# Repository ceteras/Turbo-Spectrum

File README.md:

# Turbo Spectrum aka CoBra 2

You can find out everything about Turbo Spectrum on [cobrasov.org](https://cobrasov.org), including project history, documentation, DipTrace project and gerbers, source code and binaries.  

This repo hosts the Kicad 8 port of the original project.  
This is not really ready for production, it was done for educational purposes.    

© 2022 The Cismas Foundation   
  
Mainboard render from Kicad:

This is my board, assembled from an original kit  made by the Cismas Foundation.

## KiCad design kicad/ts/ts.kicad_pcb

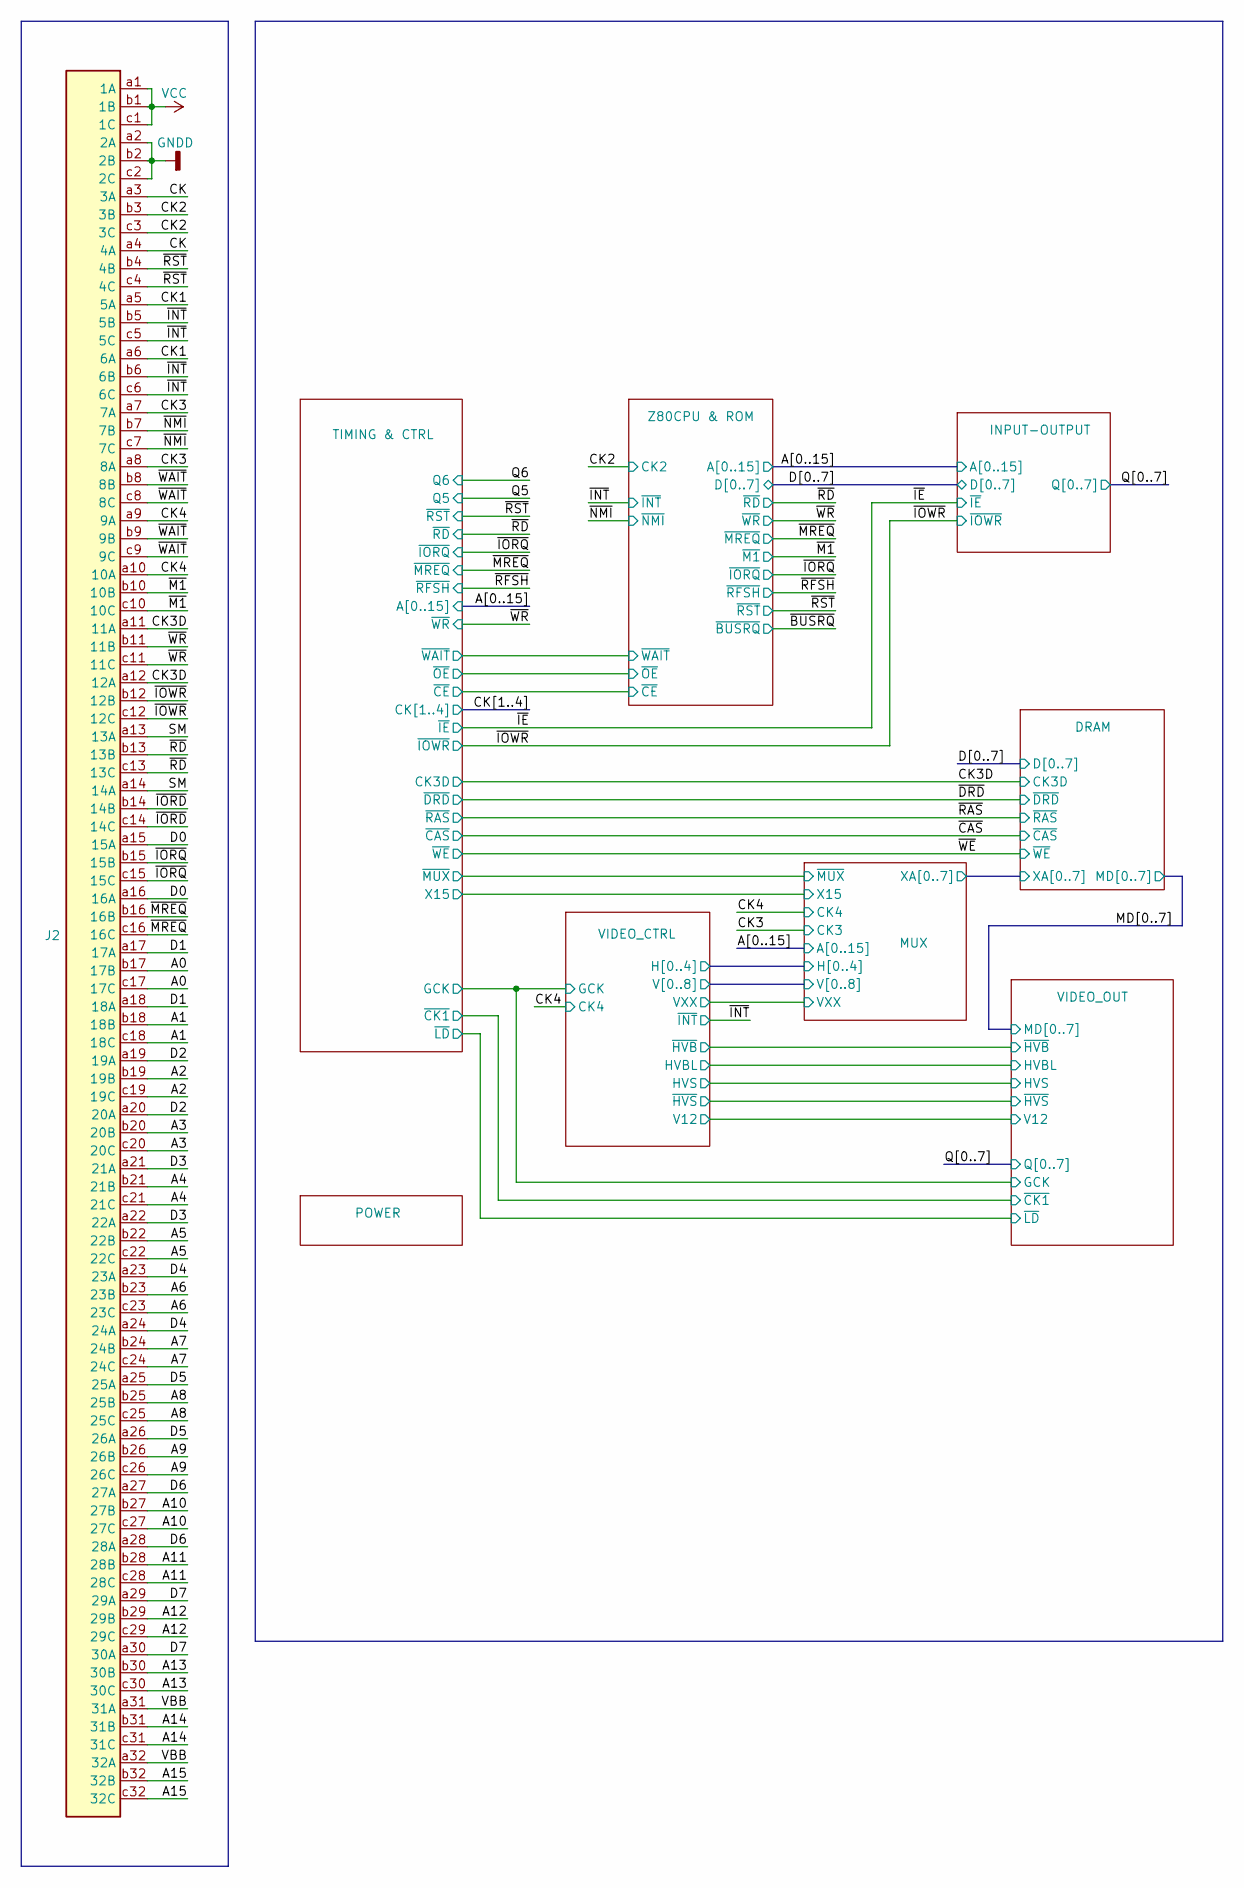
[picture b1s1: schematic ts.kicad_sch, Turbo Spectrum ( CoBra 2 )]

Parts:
J2: C96ABC; DIN41612_R_3x32_Male_Horizontal_THT

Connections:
unnamed: J2.a1 (1A), J2.b1 (1B), J2.c1 (1C)
unnamed: J2.a2 (2A), J2.b2 (2B), J2.c2 (2C)
unnamed: J2.a3 (3A), J2.a4 (4A)
unnamed: J2.a5 (5A), J2.a6 (6A)
unnamed: J2.a7 (7A), J2.a8 (8A)
unnamed: J2.a9 (9A), J2.a10 (10A)
unnamed: J2.a11 (11A), J2.a12 (12A)
unnamed: J2.a13 (13A), J2.a14 (14A)
unnamed: J2.a15 (15A), J2.a16 (16A)
unnamed: J2.a17 (17A), J2.a18 (18A)
unnamed: J2.a19 (19A), J2.a20 (20A)
unnamed: J2.a21 (21A), J2.a22 (22A)
unnamed: J2.a23 (23A), J2.a24 (24A)
unnamed: J2.a25 (25A), J2.a26 (26A)
unnamed: J2.a27 (27A), J2.a28 (28A)
unnamed: J2.a29 (29A), J2.a30 (30A)
unnamed: J2.a31 (31A), J2.a32 (32A)
unnamed: J2.b3 (3B), J2.c3 (3C)
unnamed: J2.b4 (4B), J2.c4 (4C)
unnamed: J2.b5 (5B), J2.b6 (6B), J2.c5 (5C), J2.c6 (6C)
unnamed: J2.b7 (7B), J2.c7 (7C)
unnamed: J2.b8 (8B), J2.b9 (9B), J2.c8 (8C), J2.c9 (9C)
unnamed: J2.b10 (10B), J2.c10 (10C)
unnamed: J2.b11 (11B), J2.c11 (11C)
unnamed: J2.b12 (12B), J2.c12 (12C)
unnamed: J2.b13 (13B), J2.c13 (13C)
unnamed: J2.b14 (14B), J2.c14 (14C)
unnamed: J2.b15 (15B), J2.c15 (15C)
unnamed: J2.b16 (16B), J2.c16 (16C)
unnamed: J2.b17 (17B), J2.c17 (17C)
unnamed: J2.b18 (18B), J2.c18 (18C)
unnamed: J2.b19 (19B), J2.c19 (19C)
unnamed: J2.b20 (20B), J2.c20 (20C)
unnamed: J2.b21 (21B), J2.c21 (21C)
unnamed: J2.b22 (22B), J2.c22 (22C)
unnamed: J2.b23 (23B), J2.c23 (23C)
unnamed: J2.b24 (24B), J2.c24 (24C)
unnamed: J2.b25 (25B), J2.c25 (25C)
unnamed: J2.b26 (26B), J2.c26 (26C)
unnamed: J2.b27 (27B), J2.c27 (27C)
unnamed: J2.b28 (28B), J2.c28 (28C)
unnamed: J2.b29 (29B), J2.c29 (29C)
unnamed: J2.b30 (30B), J2.c30 (30C)
unnamed: J2.b31 (31B), J2.c31 (31C)
unnamed: J2.b32 (32B), J2.c32 (32C)

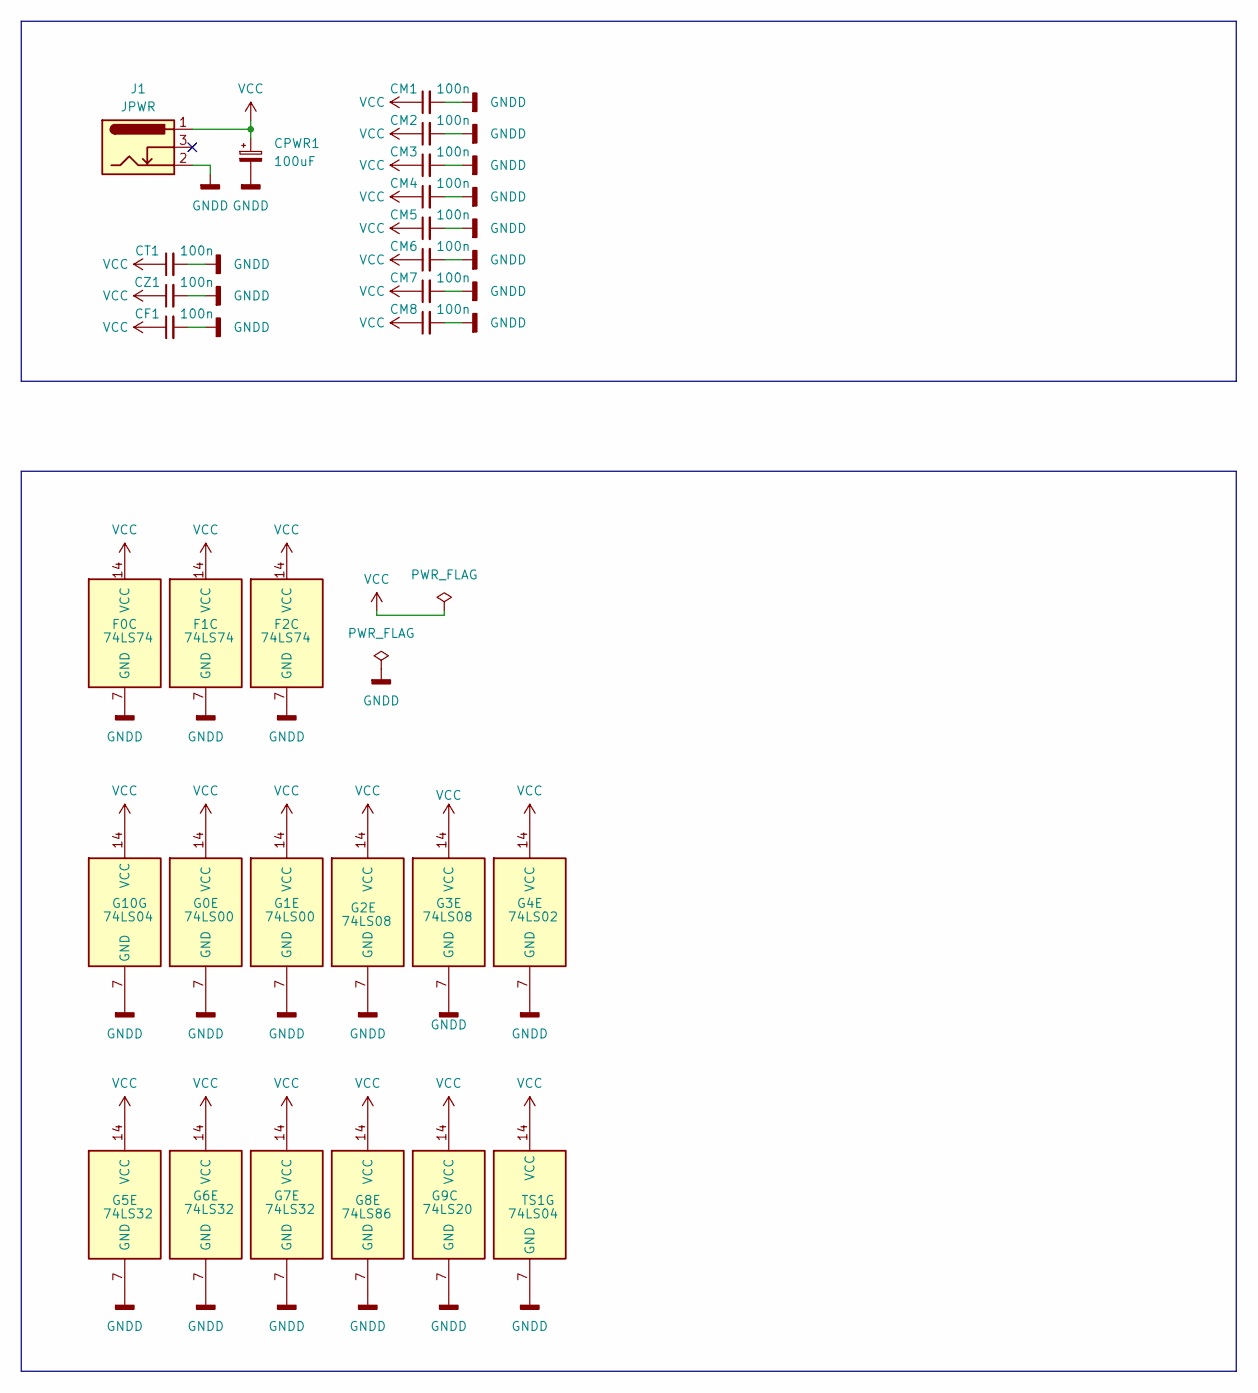
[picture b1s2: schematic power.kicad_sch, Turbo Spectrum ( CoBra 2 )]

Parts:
CF1: 100n; C_Disc_D3.0mm_W1.6mm_P2.50mm
CM1, CM2, CM3, CM4, CM5, CM6, CM7, CM8: 100n; C_Disc_D3.0mm_W1.6mm_P2.50mm
CPWR1: 100uF; CP_Radial_D10.0mm_P3.50mm
CT1: 100n; C_Disc_D3.0mm_W1.6mm_P2.50mm
CZ1: 100n; C_Disc_D3.0mm_W1.6mm_P2.50mm
F0, F1, F2: 74LS74; DIP-14_W7.62mm
G0, G1: 74LS00; DIP-14_W7.62mm
G2, G3: 74LS08; DIP-14_W7.62mm
G4: 74LS02; DIP-14_W7.62mm
G5: 74LS32
G6, G7: 74LS32; DIP-14_W7.62mm
G8: 74LS86; DIP-14_W7.62mm
G9: 74LS20; DIP-14_W7.62mm
G10: 74LS04; DIP-14_W7.62mm
J1: JPWR; BarrelJack_GCT_DCJ200-10-A_Horizontal
TS1: 74LS04; DIP-14_W7.62mm

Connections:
GNDD: CF1.2, CM1.2, CM2.2, CM3.2, CM4.2, CM5.2, CM6.2, CM7.2, CM8.2, CPWR1.2, CT1.2, CZ1.2, F0.7 (GND), F1.7 (GND), F2.7 (GND), G0.7 (GND), G1.7 (GND), G2.7 (GND), G3.7 (GND), G4.7 (GND), G5.7 (GND), G6.7 (GND), G7.7 (GND), G8.7 (GND), G9.7 (GND), G10.7 (GND), J1.2, TS1.7 (GND); also elsewhere on the board
VCC: CF1.1, CM1.1, CM2.1, CM3.1, CM4.1, CM5.1, CM6.1, CM7.1, CM8.1, CPWR1.1, CT1.1, CZ1.1, F0.14 (VCC), F1.14 (VCC), F2.14 (VCC), G0.14 (VCC), G1.14 (VCC), G2.14 (VCC), G3.14 (VCC), G4.14 (VCC), G5.14 (VCC), G6.14 (VCC), G7.14 (VCC), G8.14 (VCC), G9.14 (VCC), G10.14 (VCC), J1.1, TS1.14 (VCC); also elsewhere on the board

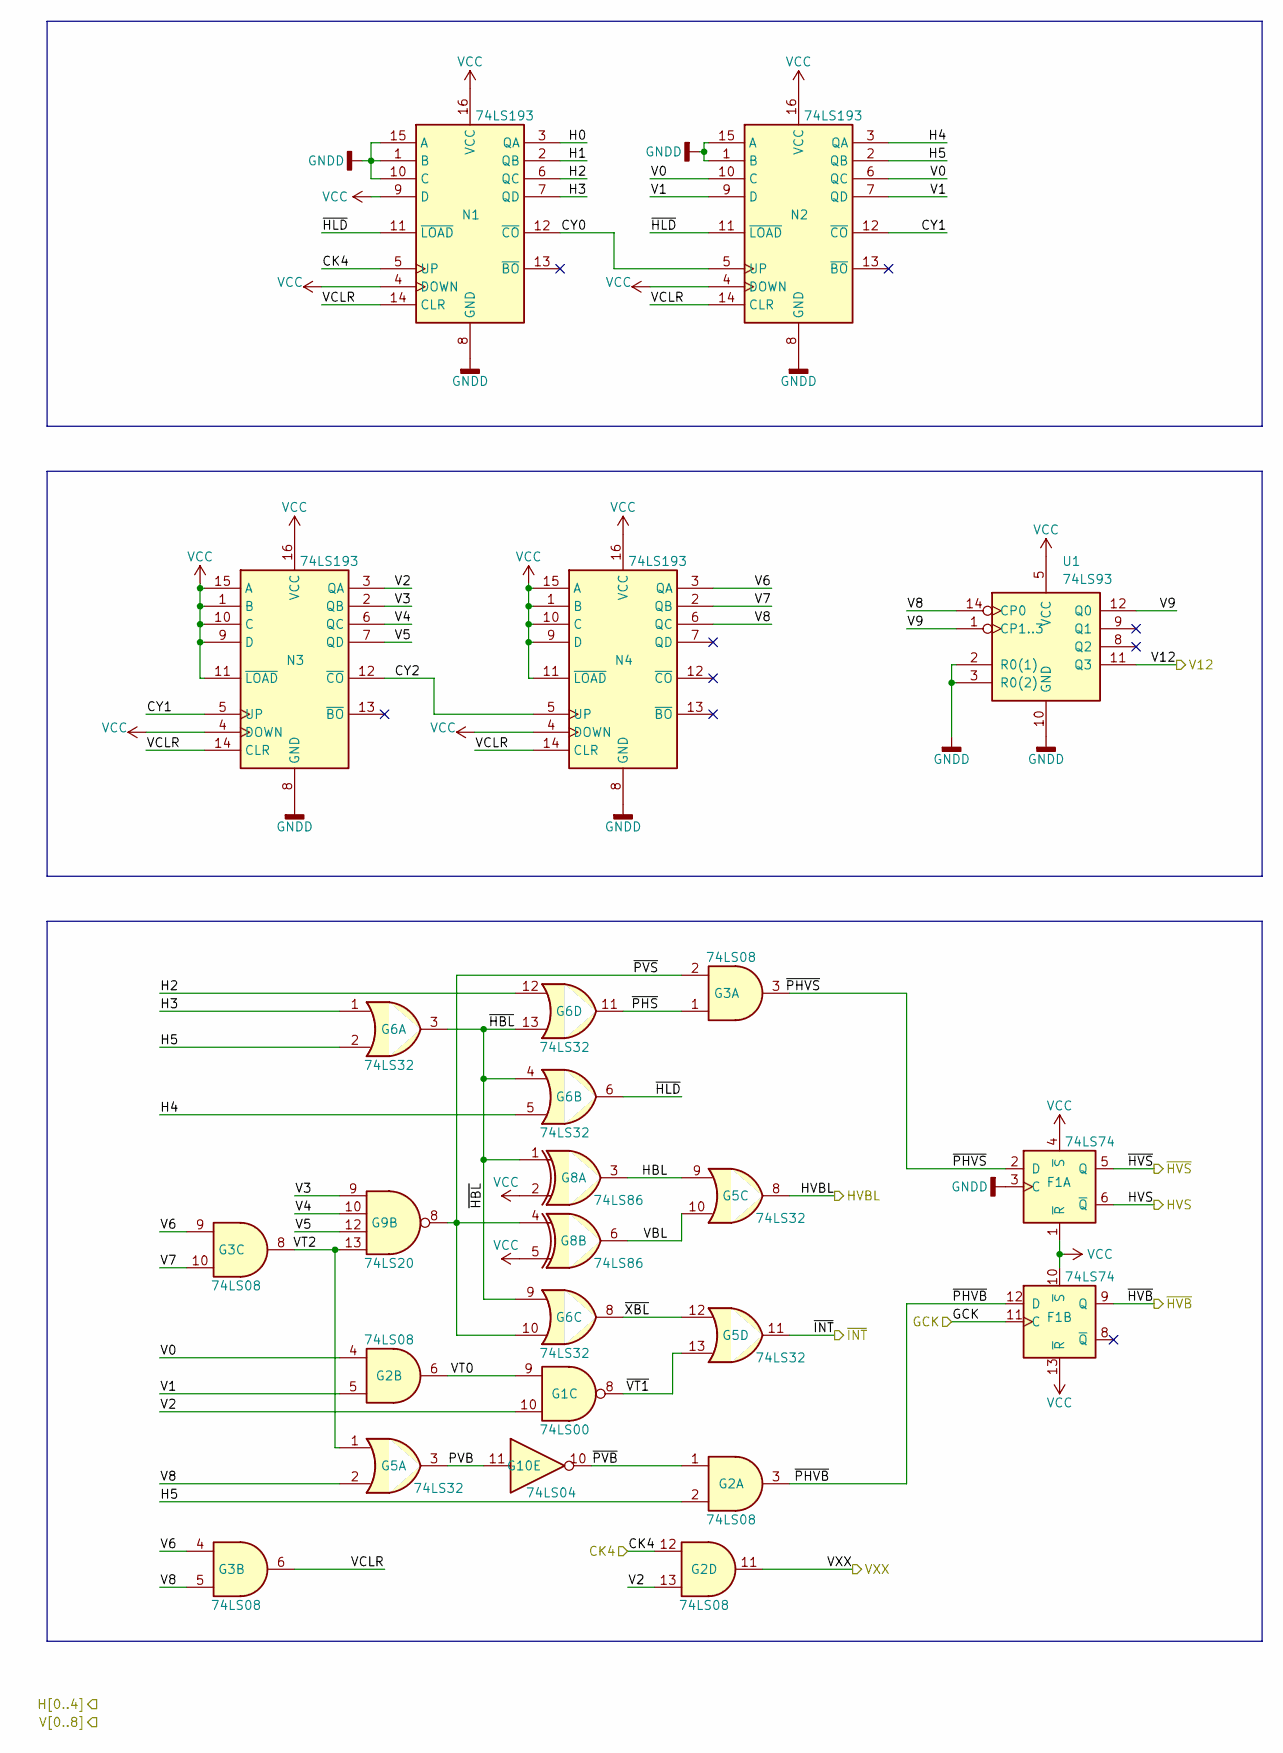
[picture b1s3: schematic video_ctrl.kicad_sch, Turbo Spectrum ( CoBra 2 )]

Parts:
F1: 74LS74; DIP-14_W7.62mm
G1: 74LS00; DIP-14_W7.62mm
G2, G3: 74LS08; DIP-14_W7.62mm
G5: 74LS32
G6: 74LS32; DIP-14_W7.62mm
G8: 74LS86; DIP-14_W7.62mm
G9: 74LS20; DIP-14_W7.62mm
G10: 74LS04; DIP-14_W7.62mm
N1, N2, N3, N4: 74LS193; DIP-16_W7.62mm
U1: 74LS93; DIP-14_W7.62mm

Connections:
/CK4: G2.12, N1.5 (UP); also elsewhere on the board
/MUX/H0: N1.3 (QA); also elsewhere on the board
/MUX/H1: N1.2 (QB); also elsewhere on the board
/MUX/H2: G6.12, N1.6 (QC); also elsewhere on the board
/MUX/H3: G6.1, N1.7 (QD); also elsewhere on the board
/MUX/H4: G6.5, N2.3 (QA); also elsewhere on the board
/MUX/V0: G2.4, N2.6 (QC), N2.10 (C); also elsewhere on the board
/MUX/V1: G2.5, N2.7 (QD), N2.9 (D); also elsewhere on the board
/MUX/V2: G1.10, G2.13, N3.3 (QA)
/MUX/V3: G9.9, N3.2 (QB); also elsewhere on the board
/MUX/V4: G9.10, N3.6 (QC); also elsewhere on the board
/MUX/V5: G9.12, N3.7 (QD); also elsewhere on the board
/MUX/V6: G3.4, G3.9, N4.3 (QA); also elsewhere on the board
/MUX/V7: G3.10, N4.2 (QB); also elsewhere on the board
/MUX/V8: G3.5, G5.2, N4.6 (QC), U1.14 (CP0)
/MUX/VXX: G2.11; also elsewhere on the board
/TIMING & CTRL/GCK: F1.11 (C); also elsewhere on the board
/VIDEO_CTRL/CY0: N1.12 (~CO), N2.5 (UP)
/VIDEO_CTRL/CY1: N2.12 (~CO), N3.5 (UP)
/VIDEO_CTRL/CY2: N3.12 (~CO), N4.5 (UP)
/VIDEO_CTRL/H5: G2.2, G6.2, N2.2 (QB)
/VIDEO_CTRL/HBL: G5.9, G8.3
/VIDEO_CTRL/HVS: F1.6 (~Q)
/VIDEO_CTRL/PVB: G5.3, G10.11
/VIDEO_CTRL/V9: U1.1 (CP1..3), U1.12 (Q0)
/VIDEO_CTRL/V12: U1.11 (Q3); also elsewhere on the board
/VIDEO_CTRL/VBL: G5.10, G8.6
/VIDEO_CTRL/VCLR: G3.6, N1.14 (CLR), N2.14 (CLR), N3.14 (CLR), N4.14 (CLR)
/VIDEO_CTRL/VT0: G1.9, G2.6
/VIDEO_CTRL/VT2: G3.8, G5.1, G9.13
/VIDEO_CTRL/~HBL: G6.3, G6.4, G6.9, G6.13, G8.1
/VIDEO_CTRL/~HLD: G6.6, N1.11 (~LOAD), N2.11 (~LOAD)
/VIDEO_CTRL/~HVB: F1.9 (Q); also elsewhere on the board
/VIDEO_CTRL/~HVS: F1.5 (Q); also elsewhere on the board
/VIDEO_CTRL/~PHS: G3.1, G6.11
/VIDEO_CTRL/~PHVB: F1.12 (D), G2.3
/VIDEO_CTRL/~PHVS: F1.2 (D), G3.3
/VIDEO_CTRL/~PVB: G2.1, G10.10
/VIDEO_CTRL/~PVS: G3.2, G6.10, G8.4, G9.8
/VIDEO_CTRL/~VT1: G1.8, G5.13
/VIDEO_CTRL/~XBL: G5.12, G6.8
GNDD: F1.3 (C), N1.1 (B), N1.8 (GND), N1.10 (C), N1.15 (A), N2.1 (B), N2.8 (GND), N2.15 (A), N3.8 (GND), N4.8 (GND), U1.2 (R0(1)), U1.3 (R0(2)), U1.10 (GND); also elsewhere on the board
VCC: F1.1 (~R), F1.4 (~S), F1.10 (~S), F1.13 (~R), G8.2, G8.5, N1.4 (DOWN), N1.9 (D), N1.16 (VCC), N2.4 (DOWN), N2.16 (VCC), N3.1 (B), N3.4 (DOWN), N3.9 (D), N3.10 (C), N3.11 (~LOAD), N3.15 (A), N3.16 (VCC), N4.1 (B), N4.4 (DOWN), N4.9 (D), N4.10 (C), N4.11 (~LOAD), N4.15 (A), N4.16 (VCC), U1.5 (VCC); also elsewhere on the board

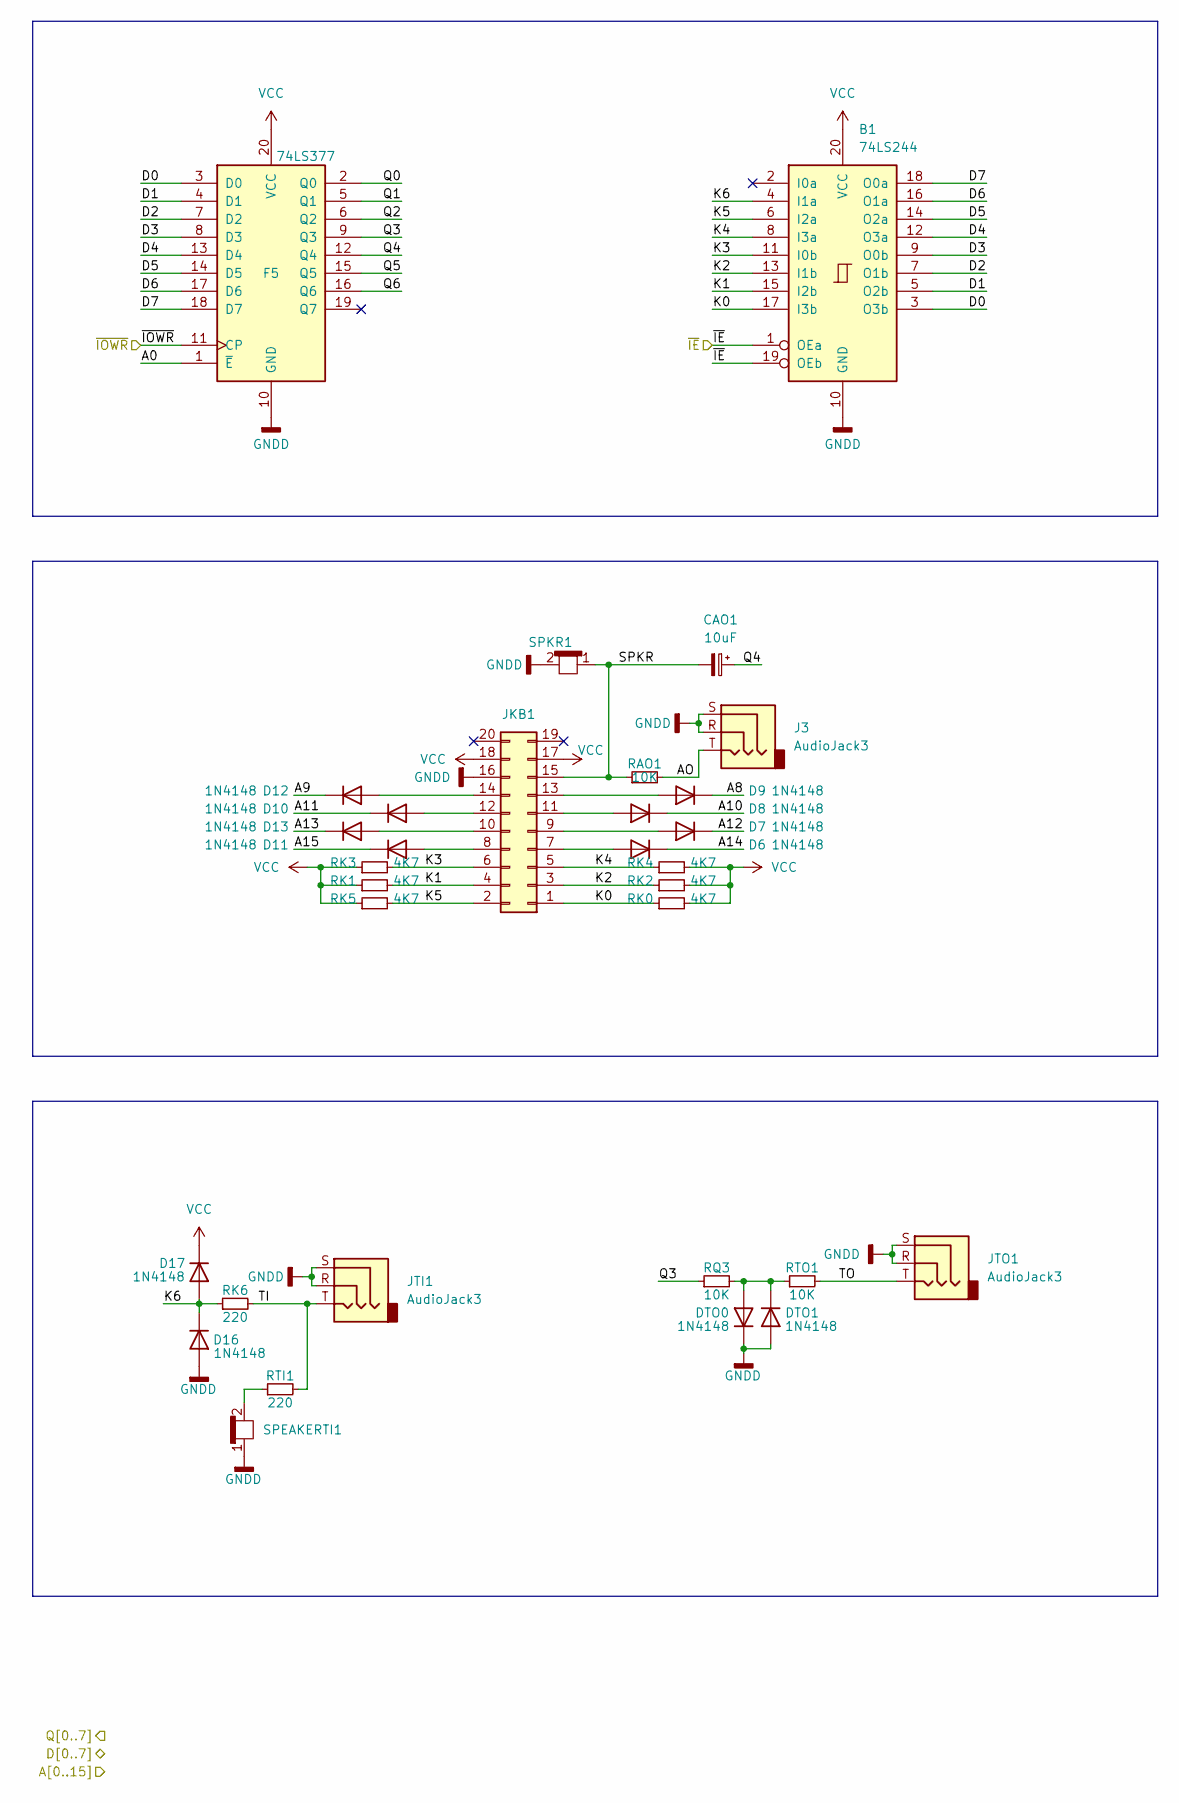
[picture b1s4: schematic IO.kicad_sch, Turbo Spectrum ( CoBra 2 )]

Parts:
B1: 74LS244; DIP-20_W7.62mm
CAO1: 10uF
D6, D7, D8, D9, D10, D11, D12, D13, D16, D17: 1N4148; D_DO-35_SOD27_P7.62mm_Horizontal
DTO0, DTO1: 1N4148; D_DO-35_SOD27_P7.62mm_Horizontal
F5: 74LS377; DIP-20_W7.62mm
J3: AudioJack3
JKB1: Conn_02x10_Odd_Even
JTI1: AudioJack3
JTO1: AudioJack3
RAO1: 10K; R_Axial_DIN0204_L3.6mm_D1.6mm_P7.62mm_Horizontal
RK0, RK1, RK2, RK3, RK4, RK5: 4K7; R_Axial_DIN0204_L3.6mm_D1.6mm_P7.62mm_Horizontal
RK6: 220; R_Axial_DIN0204_L3.6mm_D1.6mm_P7.62mm_Horizontal
RQ3: 10K; R_Axial_DIN0204_L3.6mm_D1.6mm_P7.62mm_Horizontal
RTI1: 220; R_Axial_DIN0204_L3.6mm_D1.6mm_P7.62mm_Horizontal
RTO1: 10K; R_Axial_DIN0204_L3.6mm_D1.6mm_P7.62mm_Horizontal
SPEAKERTI1: Earphone
SPKR1: Earphone

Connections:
/A0: F5.1 (~E); also elsewhere on the board
/A8: D9.1 (K); also elsewhere on the board
/A9: D12.1 (K); also elsewhere on the board
/A10: D8.1 (K); also elsewhere on the board
/A11: D10.1 (K); also elsewhere on the board
/A12: D7.1 (K); also elsewhere on the board
/A13: D13.1 (K); also elsewhere on the board
/A14: D6.1 (K); also elsewhere on the board
/A15: D11.1 (K); also elsewhere on the board
/D0: B1.3 (O3b), F5.3 (D0); also elsewhere on the board
/D1: B1.5 (O2b), F5.4 (D1); also elsewhere on the board
/D2: B1.7 (O1b), F5.7 (D2); also elsewhere on the board
/D3: B1.9 (O0b), F5.8 (D3); also elsewhere on the board
/D4: B1.12 (O3a), F5.13 (D4); also elsewhere on the board
/D5: B1.14 (O2a), F5.14 (D5); also elsewhere on the board
/D6: B1.16 (O1a), F5.17 (D6); also elsewhere on the board
/D7: B1.18 (O0a), F5.18 (D7); also elsewhere on the board
/INPUT-OUTPUT/AO: J3.T, RAO1.2
/INPUT-OUTPUT/K0: B1.17 (I3b), JKB1.1, RK0.1
/INPUT-OUTPUT/K1: B1.15 (I2b), JKB1.4, RK1.2
/INPUT-OUTPUT/K2: B1.13 (I1b), JKB1.3, RK2.1
/INPUT-OUTPUT/K3: B1.11 (I0b), JKB1.6, RK3.2
/INPUT-OUTPUT/K4: B1.8 (I3a), JKB1.5, RK4.1
/INPUT-OUTPUT/K5: B1.6 (I2a), JKB1.2, RK5.2
/INPUT-OUTPUT/K6: B1.4 (I1a), D16.1 (K), D17.2 (A), RK6.1
/INPUT-OUTPUT/SPKR: CAO1.2, JKB1.15, RAO1.1, SPKR1.1 (-)
/INPUT-OUTPUT/TI: JTI1.T, RK6.2, RTI1.2
/INPUT-OUTPUT/TO: JTO1.T, RTO1.2
/Q0: F5.2 (Q0); also elsewhere on the board
/Q1: F5.5 (Q1); also elsewhere on the board
/Q2: F5.6 (Q2); also elsewhere on the board
/Q3: F5.9 (Q3), RQ3.1
/Q4: CAO1.1, F5.12 (Q4)
/Q5: F5.15 (Q5); also elsewhere on the board
/Q6: F5.16 (Q6); also elsewhere on the board
/~IE: B1.1 (OEa), B1.19 (OEb); also elsewhere on the board
/~IOWR: F5.11 (CP); also elsewhere on the board
GNDD: B1.10 (GND), D16.2 (A), DTO0.1 (K), DTO1.2 (A), F5.10 (GND), J3.R, J3.S, JKB1.16, JTI1.R, JTI1.S, JTO1.R, JTO1.S, SPEAKERTI1.1 (-), SPKR1.2 (+); also elsewhere on the board
unnamed: D6.2 (A), JKB1.7
unnamed: D7.2 (A), JKB1.9
unnamed: D8.2 (A), JKB1.11
unnamed: D9.2 (A), JKB1.13
unnamed: D10.2 (A), JKB1.12
unnamed: D11.2 (A), JKB1.8
unnamed: D12.2 (A), JKB1.14
unnamed: D13.2 (A), JKB1.10
unnamed: DTO0.2 (A), DTO1.1 (K), RQ3.2, RTO1.1
unnamed: RTI1.1, SPEAKERTI1.2 (+)
VCC: B1.20 (VCC), D17.1 (K), F5.20 (VCC), JKB1.17, JKB1.18, RK0.2, RK1.1, RK2.2, RK3.1, RK4.2, RK5.1; also elsewhere on the board

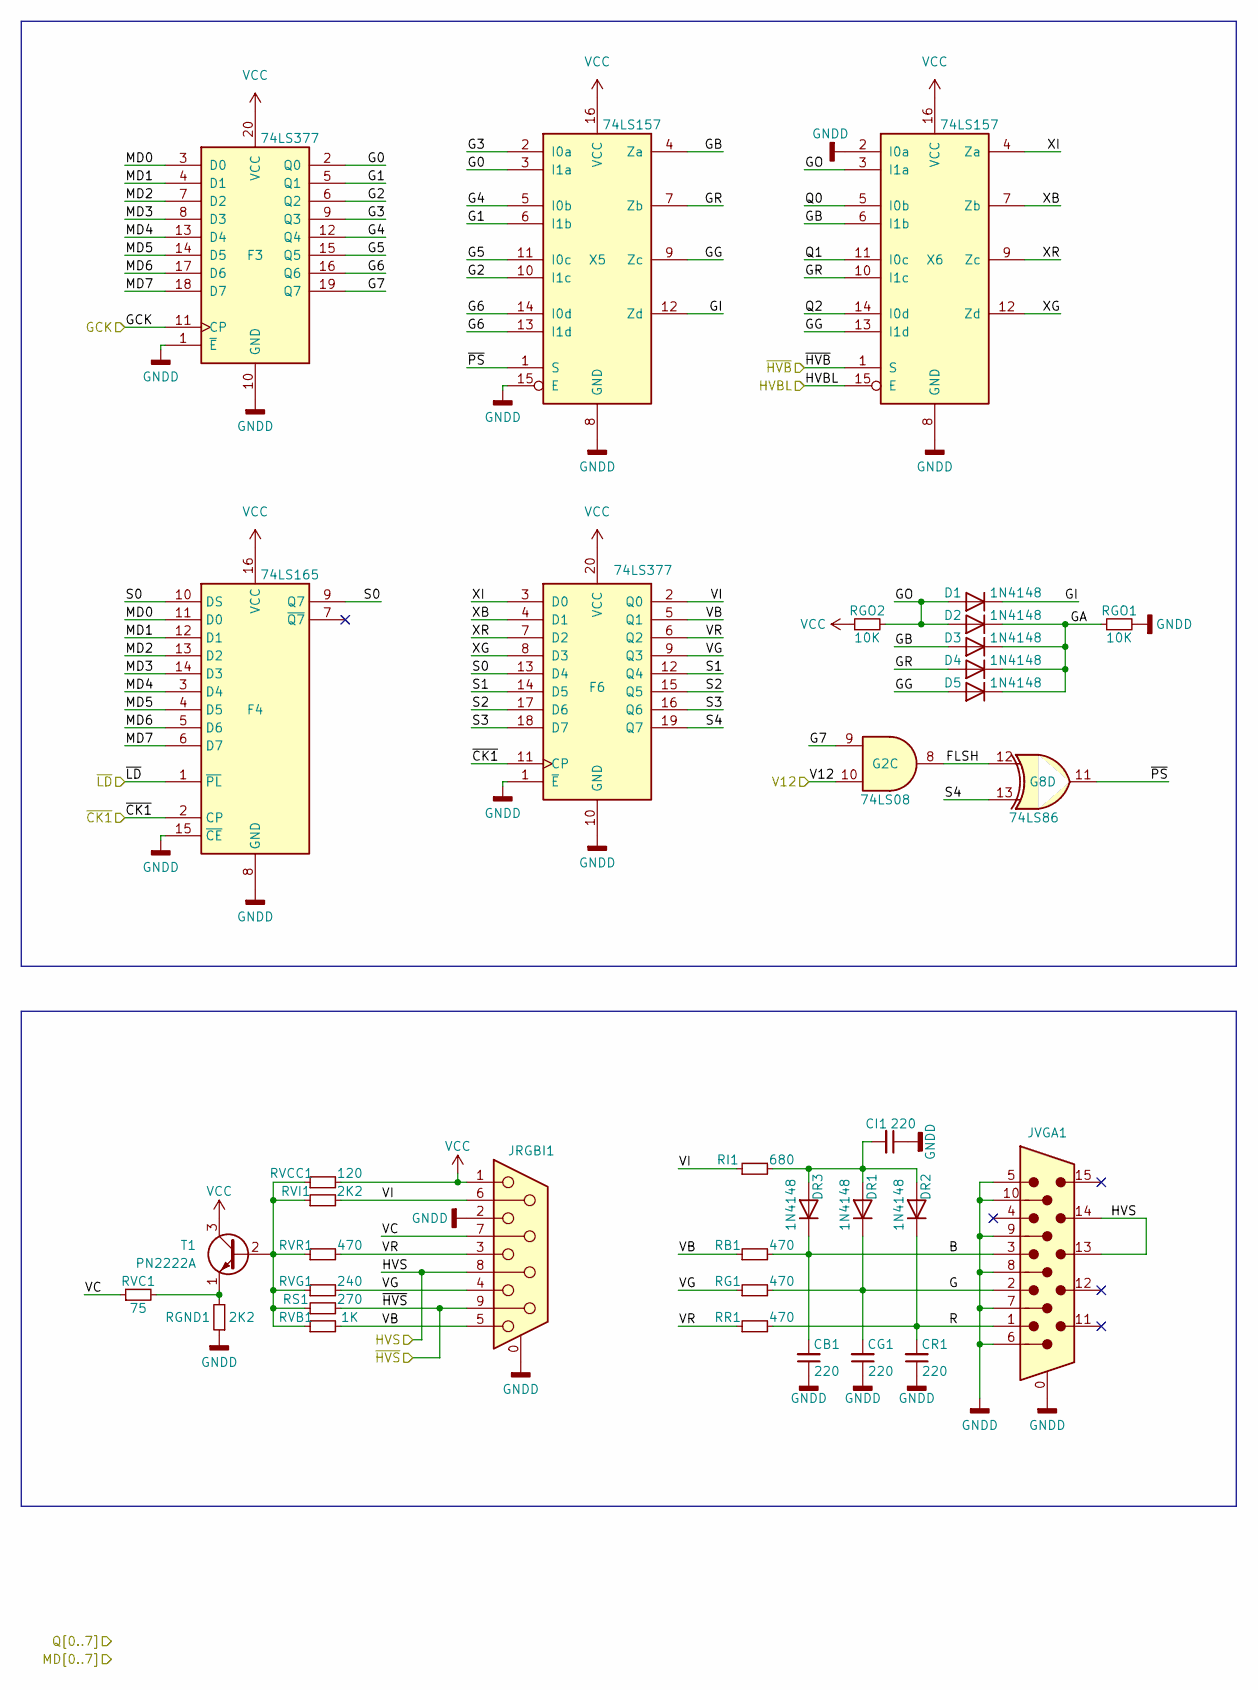
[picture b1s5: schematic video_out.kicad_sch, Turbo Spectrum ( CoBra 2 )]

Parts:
CB1: 220; C_Disc_D3.0mm_W1.6mm_P2.50mm
CG1: 220; C_Disc_D3.0mm_W1.6mm_P2.50mm
CI1: 220; C_Disc_D3.0mm_W1.6mm_P2.50mm
CR1: 220; C_Disc_D3.0mm_W1.6mm_P2.50mm
D1, D2, D3, D4, D5: 1N4148; D_DO-35_SOD27_P7.62mm_Horizontal
DR1, DR2, DR3: 1N4148; D_DO-35_SOD27_P7.62mm_Horizontal
F3, F6: 74LS377; DIP-20_W7.62mm
F4: 74LS165; DIP-16_W7.62mm
G2: 74LS08; DIP-14_W7.62mm
G8: 74LS86; DIP-14_W7.62mm
JRGBI1: DE9_Receptacle_MountingHoles
JVGA1: DE15_Plug_HighDensity_MountingHoles
RB1: 470; R_Axial_DIN0204_L3.6mm_D1.6mm_P7.62mm_Horizontal
RG1: 470; R_Axial_DIN0204_L3.6mm_D1.6mm_P7.62mm_Horizontal
RGND1: 2K2; R_Axial_DIN0204_L3.6mm_D1.6mm_P7.62mm_Horizontal
RGO1, RGO2: 10K; R_Axial_DIN0204_L3.6mm_D1.6mm_P7.62mm_Horizontal
RI1: 680; R_Axial_DIN0204_L3.6mm_D1.6mm_P7.62mm_Horizontal
RR1: 470; R_Axial_DIN0204_L3.6mm_D1.6mm_P7.62mm_Horizontal
RS1: 270; R_Axial_DIN0204_L3.6mm_D1.6mm_P7.62mm_Horizontal
RVB1: 1K; R_Axial_DIN0204_L3.6mm_D1.6mm_P7.62mm_Horizontal
RVC1: 75; R_Axial_DIN0204_L3.6mm_D1.6mm_P7.62mm_Horizontal
RVCC1: 120; R_Axial_DIN0204_L3.6mm_D1.6mm_P7.62mm_Horizontal
RVG1: 240; R_Axial_DIN0204_L3.6mm_D1.6mm_P7.62mm_Horizontal
RVI1: 2K2; R_Axial_DIN0204_L3.6mm_D1.6mm_P7.62mm_Horizontal
RVR1: 470; R_Axial_DIN0204_L3.6mm_D1.6mm_P7.62mm_Horizontal
T1: PN2222A; TO-92_Inline
X5, X6: 74LS157; DIP-16_W7.62mm

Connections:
/MD0: F3.3 (D0), F4.11 (D0); also elsewhere on the board
/MD1: F3.4 (D1), F4.12 (D1); also elsewhere on the board
/MD2: F3.7 (D2), F4.13 (D2); also elsewhere on the board
/MD3: F3.8 (D3), F4.14 (D3); also elsewhere on the board
/MD4: F3.13 (D4), F4.3 (D4); also elsewhere on the board
/MD5: F3.14 (D5), F4.4 (D5); also elsewhere on the board
/MD6: F3.17 (D6), F4.5 (D6); also elsewhere on the board
/MD7: F3.18 (D7), F4.6 (D7); also elsewhere on the board
/Q0: X6.5 (I0b); also elsewhere on the board
/Q1: X6.11 (I0c); also elsewhere on the board
/Q2: X6.14 (I0d); also elsewhere on the board
/TIMING & CTRL/GCK: F3.11 (CP); also elsewhere on the board
/TIMING & CTRL/~CK1: F4.2 (CP), F6.11 (CP); also elsewhere on the board
/TIMING & CTRL/~LD: F4.1 (~PL); also elsewhere on the board
/VIDEO_CTRL/HVBL: X6.15 (E)
/VIDEO_CTRL/V12: G2.10; also elsewhere on the board
/VIDEO_CTRL/~HVB: X6.1 (S); also elsewhere on the board
/VIDEO_CTRL/~HVS: JRGBI1.9, RS1.2; also elsewhere on the board
/VIDEO_OUT/B: CB1.2, DR3.1 (K), JVGA1.3, RB1.2
/VIDEO_OUT/FLSH: G2.8, G8.12
/VIDEO_OUT/G: CG1.2, DR1.1 (K), JVGA1.2, RG1.2
/VIDEO_OUT/G0: F3.2 (Q0), X5.3 (I1a)
/VIDEO_OUT/G1: F3.5 (Q1), X5.6 (I1b)
/VIDEO_OUT/G2: F3.6 (Q2), X5.10 (I1c)
/VIDEO_OUT/G3: F3.9 (Q3), X5.2 (I0a)
/VIDEO_OUT/G4: F3.12 (Q4), X5.5 (I0b)
/VIDEO_OUT/G5: F3.15 (Q5), X5.11 (I0c)
/VIDEO_OUT/G6: F3.16 (Q6), X5.13 (I1d), X5.14 (I0d)
/VIDEO_OUT/G7: F3.19 (Q7), G2.9
/VIDEO_OUT/GA: D2.1 (K), D3.1 (K), D4.1 (K), D5.1 (K), RGO1.1
/VIDEO_OUT/GB: D3.2 (A), X5.4 (Za), X6.6 (I1b)
/VIDEO_OUT/GG: D5.2 (A), X5.9 (Zc), X6.13 (I1d)
/VIDEO_OUT/GI: D1.1 (K), X5.12 (Zd)
/VIDEO_OUT/GO: D1.2 (A), D2.2 (A), RGO2.2, X6.3 (I1a)
/VIDEO_OUT/GR: D4.2 (A), X5.7 (Zb), X6.10 (I1c)
/VIDEO_OUT/R: CR1.2, DR2.1 (K), JVGA1.1, RR1.2
/VIDEO_OUT/S0: F4.9 (Q7), F4.10 (DS), F6.13 (D4)
/VIDEO_OUT/S1: F6.12 (Q4), F6.14 (D5)
/VIDEO_OUT/S2: F6.15 (Q5), F6.17 (D6)
/VIDEO_OUT/S3: F6.16 (Q6), F6.18 (D7)
/VIDEO_OUT/S4: F6.19 (Q7), G8.13
/VIDEO_OUT/VB: F6.5 (Q1), JRGBI1.5, RB1.1, RVB1.2
/VIDEO_OUT/VC: JRGBI1.7, RVC1.1
/VIDEO_OUT/VG: F6.9 (Q3), JRGBI1.4, RG1.1, RVG1.2
/VIDEO_OUT/VI: F6.2 (Q0), JRGBI1.6, RI1.1, RVI1.2
/VIDEO_OUT/VR: F6.6 (Q2), JRGBI1.3, RR1.1, RVR1.2
/VIDEO_OUT/XB: F6.4 (D1), X6.7 (Zb)
/VIDEO_OUT/XG: F6.8 (D3), X6.12 (Zd)
/VIDEO_OUT/XI: F6.3 (D0), X6.4 (Za)
/VIDEO_OUT/XR: F6.7 (D2), X6.9 (Zc)
/VIDEO_OUT/~PS: G8.11, X5.1 (S)
GNDD: CB1.1, CG1.1, CI1.1, CR1.1, F3.1 (~E), F3.10 (GND), F4.8 (GND), F4.15 (~CE), F6.1 (~E), F6.10 (GND), JRGBI1.0 (PAD), JRGBI1.2, JVGA1.0, JVGA1.5, JVGA1.6, JVGA1.7, JVGA1.8, JVGA1.9, JVGA1.10, RGND1.1, RGO1.2, X5.8 (GND), X5.15 (E), X6.2 (I0a), X6.8 (GND); also elsewhere on the board
unnamed: CI1.2, DR1.2 (A), DR2.2 (A), DR3.2 (A), RI1.2
unnamed: JRGBI1.8, JVGA1.13, JVGA1.14
unnamed: RS1.1, RVB1.1, RVCC1.1, RVG1.1, RVI1.1, RVR1.1, T1.2 (B)
unnamed: RGND1.2, RVC1.2, T1.1 (E)
VCC: F3.20 (VCC), F4.16 (VCC), F6.20 (VCC), JRGBI1.1, RGO2.1, RVCC1.2, T1.3 (C), X5.16 (VCC), X6.16 (VCC); also elsewhere on the board

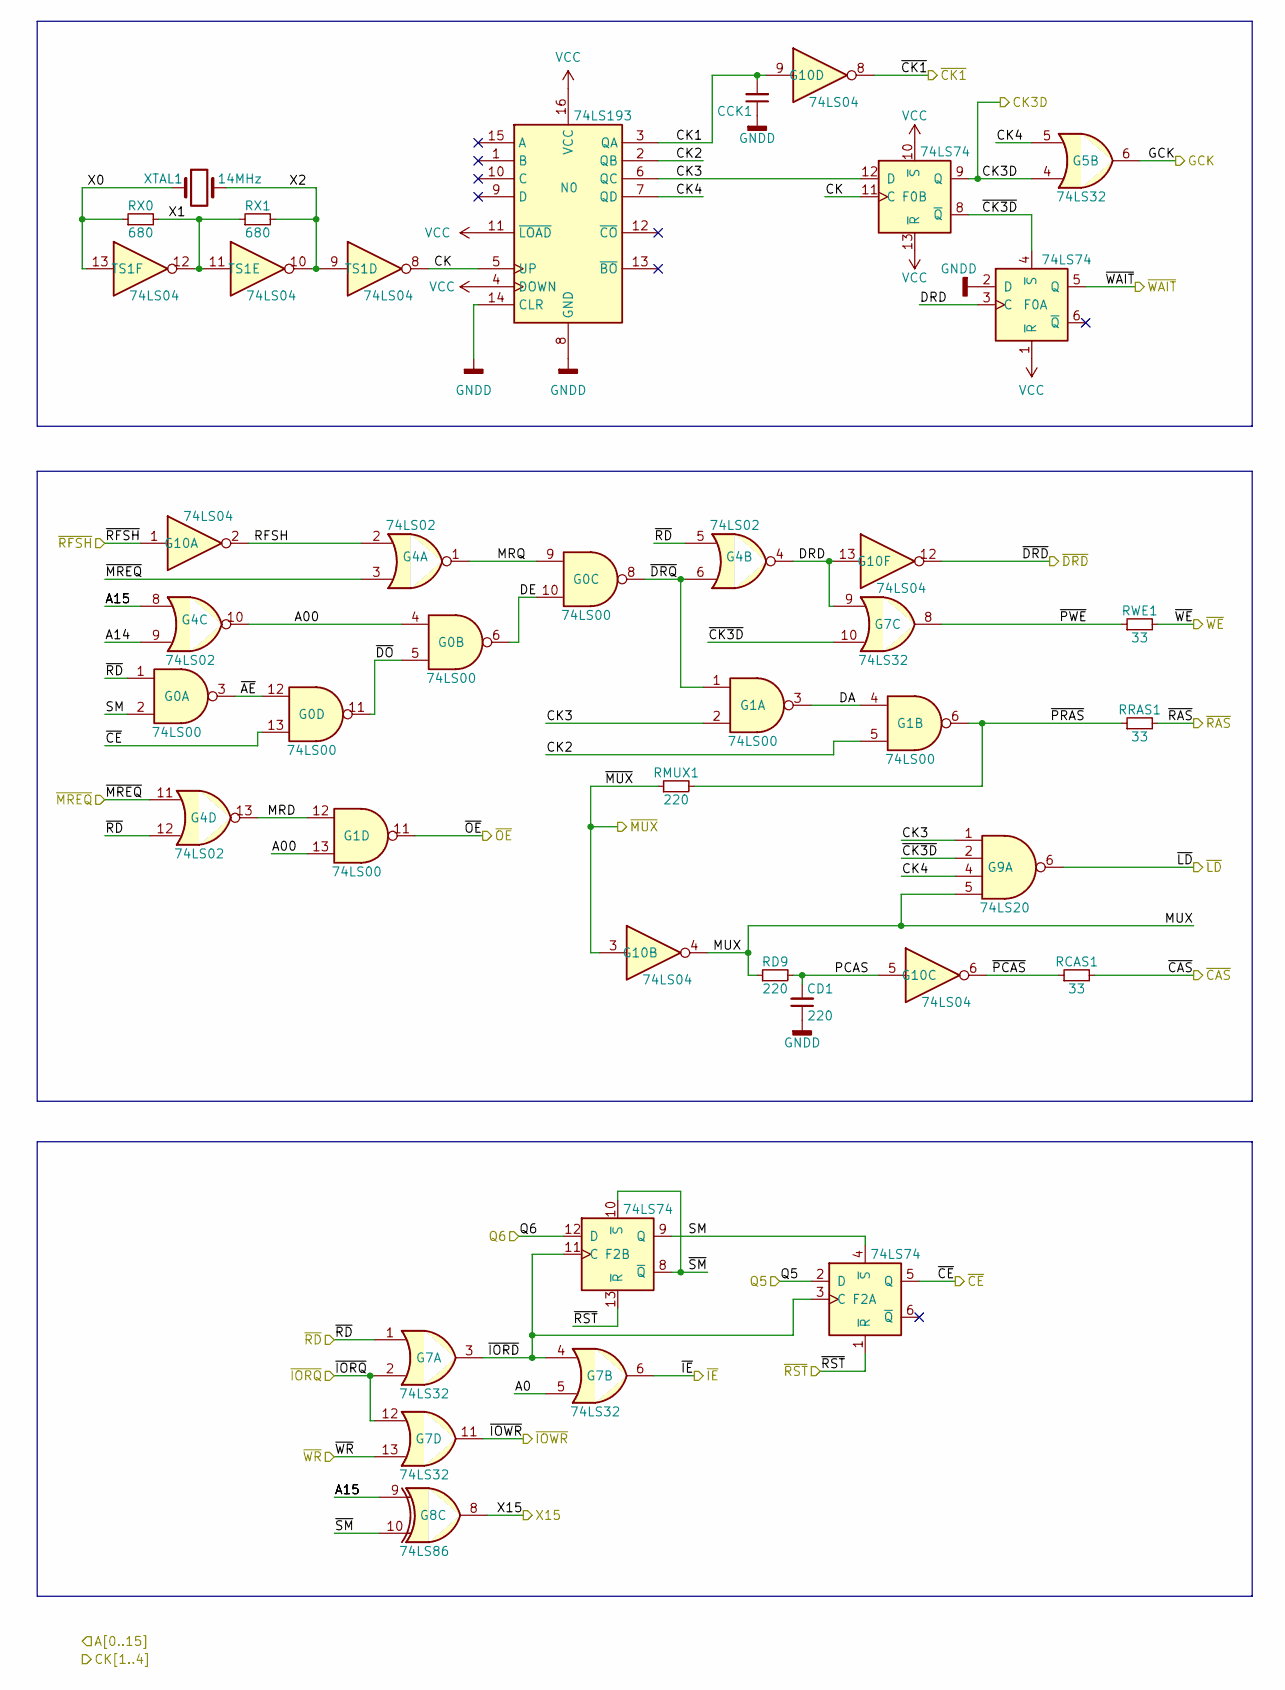
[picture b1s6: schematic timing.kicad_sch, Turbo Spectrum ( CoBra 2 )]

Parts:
CCK1: C_Disc_D3.0mm_W1.6mm_P2.50mm
CD1: 220; C_Disc_D3.0mm_W1.6mm_P2.50mm
F0, F2: 74LS74; DIP-14_W7.62mm
G0, G1: 74LS00; DIP-14_W7.62mm
G4: 74LS02; DIP-14_W7.62mm
G5: 74LS32
G7: 74LS32; DIP-14_W7.62mm
G8: 74LS86; DIP-14_W7.62mm
G9: 74LS20; DIP-14_W7.62mm
G10: 74LS04; DIP-14_W7.62mm
N0: 74LS193; DIP-16_W7.62mm
RCAS1: 33; R_Axial_DIN0204_L3.6mm_D1.6mm_P7.62mm_Horizontal
RD9: 220; R_Axial_DIN0204_L3.6mm_D1.6mm_P7.62mm_Horizontal
RMUX1: 220; R_Axial_DIN0204_L3.6mm_D1.6mm_P7.62mm_Horizontal
RRAS1: 33; R_Axial_DIN0204_L3.6mm_D1.6mm_P7.62mm_Horizontal
RWE1: 33; R_Axial_DIN0204_L3.6mm_D1.6mm_P7.62mm_Horizontal
RX0, RX1: 680; R_Axial_DIN0204_L3.6mm_D1.6mm_P7.62mm_Horizontal
TS1: 74LS04; DIP-14_W7.62mm
XTAL1: 14MHz; Crystal_HC18-U_Vertical

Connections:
/A0: G7.5; also elsewhere on the board
/A14: G4.9; also elsewhere on the board
/A15: G4.8, G8.9; also elsewhere on the board
/CK1: CCK1.2, G10.9, N0.3 (QA)
/CK2: G1.5, N0.2 (QB); also elsewhere on the board
/CK3: F0.12 (D), G1.2, G9.1, N0.6 (QC); also elsewhere on the board
/CK3D: F0.9 (Q), G5.4; also elsewhere on the board
/CK4: G5.5, G9.4, N0.7 (QD); also elsewhere on the board
/MUX/X15: G8.8; also elsewhere on the board
/MUX/~MUX: G10.3, RMUX1.1; also elsewhere on the board
/Q5: F2.2 (D); also elsewhere on the board
/Q6: F2.12 (D); also elsewhere on the board
/TIMING & CTRL/A00: G0.4, G1.13, G4.10
/TIMING & CTRL/CK: F0.11 (C), N0.5 (UP), TS1.8
/TIMING & CTRL/DA: G1.3, G1.4
/TIMING & CTRL/DE: G0.6, G0.10
/TIMING & CTRL/DRD: F0.3 (C), G4.4, G7.9, G10.13
/TIMING & CTRL/MRD: G1.12, G4.13
/TIMING & CTRL/MRQ: G0.9, G4.1
/TIMING & CTRL/MUX: G9.5, G10.4, RD9.1
/TIMING & CTRL/PCAS: CD1.2, G10.5, RD9.2
/TIMING & CTRL/RFSH: G4.2, G10.2
/TIMING & CTRL/SM: F2.4 (~S), F2.9 (Q), G0.2
/TIMING & CTRL/X0: RX0.1, TS1.13, XTAL1.1
/TIMING & CTRL/X1: RX0.2, RX1.1, TS1.11, TS1.12
/TIMING & CTRL/X2: RX1.2, TS1.9, TS1.10, XTAL1.2
/TIMING & CTRL/~AE: G0.3, G0.12
/TIMING & CTRL/~CE: F2.5 (Q), G0.13; also elsewhere on the board
/TIMING & CTRL/~CK1: G10.8; also elsewhere on the board
/TIMING & CTRL/~CK3D: F0.4 (~S), F0.8 (~Q), G7.10, G9.2
/TIMING & CTRL/~DO: G0.5, G0.11
/TIMING & CTRL/~DRQ: G0.8, G1.1, G4.6
/TIMING & CTRL/~IORD: F2.3 (C), F2.11 (C), G7.3, G7.4
/TIMING & CTRL/~LD: G9.6; also elsewhere on the board
/TIMING & CTRL/~OE: G1.11; also elsewhere on the board
/TIMING & CTRL/~PCAS: G10.6, RCAS1.1
/TIMING & CTRL/~PRAS: G1.6, RMUX1.2, RRAS1.1
/TIMING & CTRL/~PWE: G7.8, RWE1.1
/TIMING & CTRL/~SM: F2.8 (~Q), F2.10 (~S), G8.10
/TIMING & CTRL/~WAIT: F0.5 (Q); also elsewhere on the board
/~CAS: RCAS1.2; also elsewhere on the board
/~DRD: G10.12; also elsewhere on the board
/~IE: G7.6; also elsewhere on the board
/~IORQ: G7.2, G7.12; also elsewhere on the board
/~IOWR: G7.11; also elsewhere on the board
/~MREQ: G4.3, G4.11; also elsewhere on the board
/~RAS: RRAS1.2; also elsewhere on the board
/~RD: G0.1, G4.5, G4.12, G7.1; also elsewhere on the board
/~RFSH: G10.1; also elsewhere on the board
/~RST: F2.1 (~R), F2.13 (~R); also elsewhere on the board
/~WE: RWE1.2; also elsewhere on the board
/~WR: G7.13; also elsewhere on the board
GNDD: CCK1.1, CD1.1, F0.2 (D), N0.8 (GND), N0.14 (CLR); also elsewhere on the board
VCC: F0.1 (~R), F0.10 (~S), F0.13 (~R), N0.4 (DOWN), N0.11 (~LOAD), N0.16 (VCC); also elsewhere on the board
